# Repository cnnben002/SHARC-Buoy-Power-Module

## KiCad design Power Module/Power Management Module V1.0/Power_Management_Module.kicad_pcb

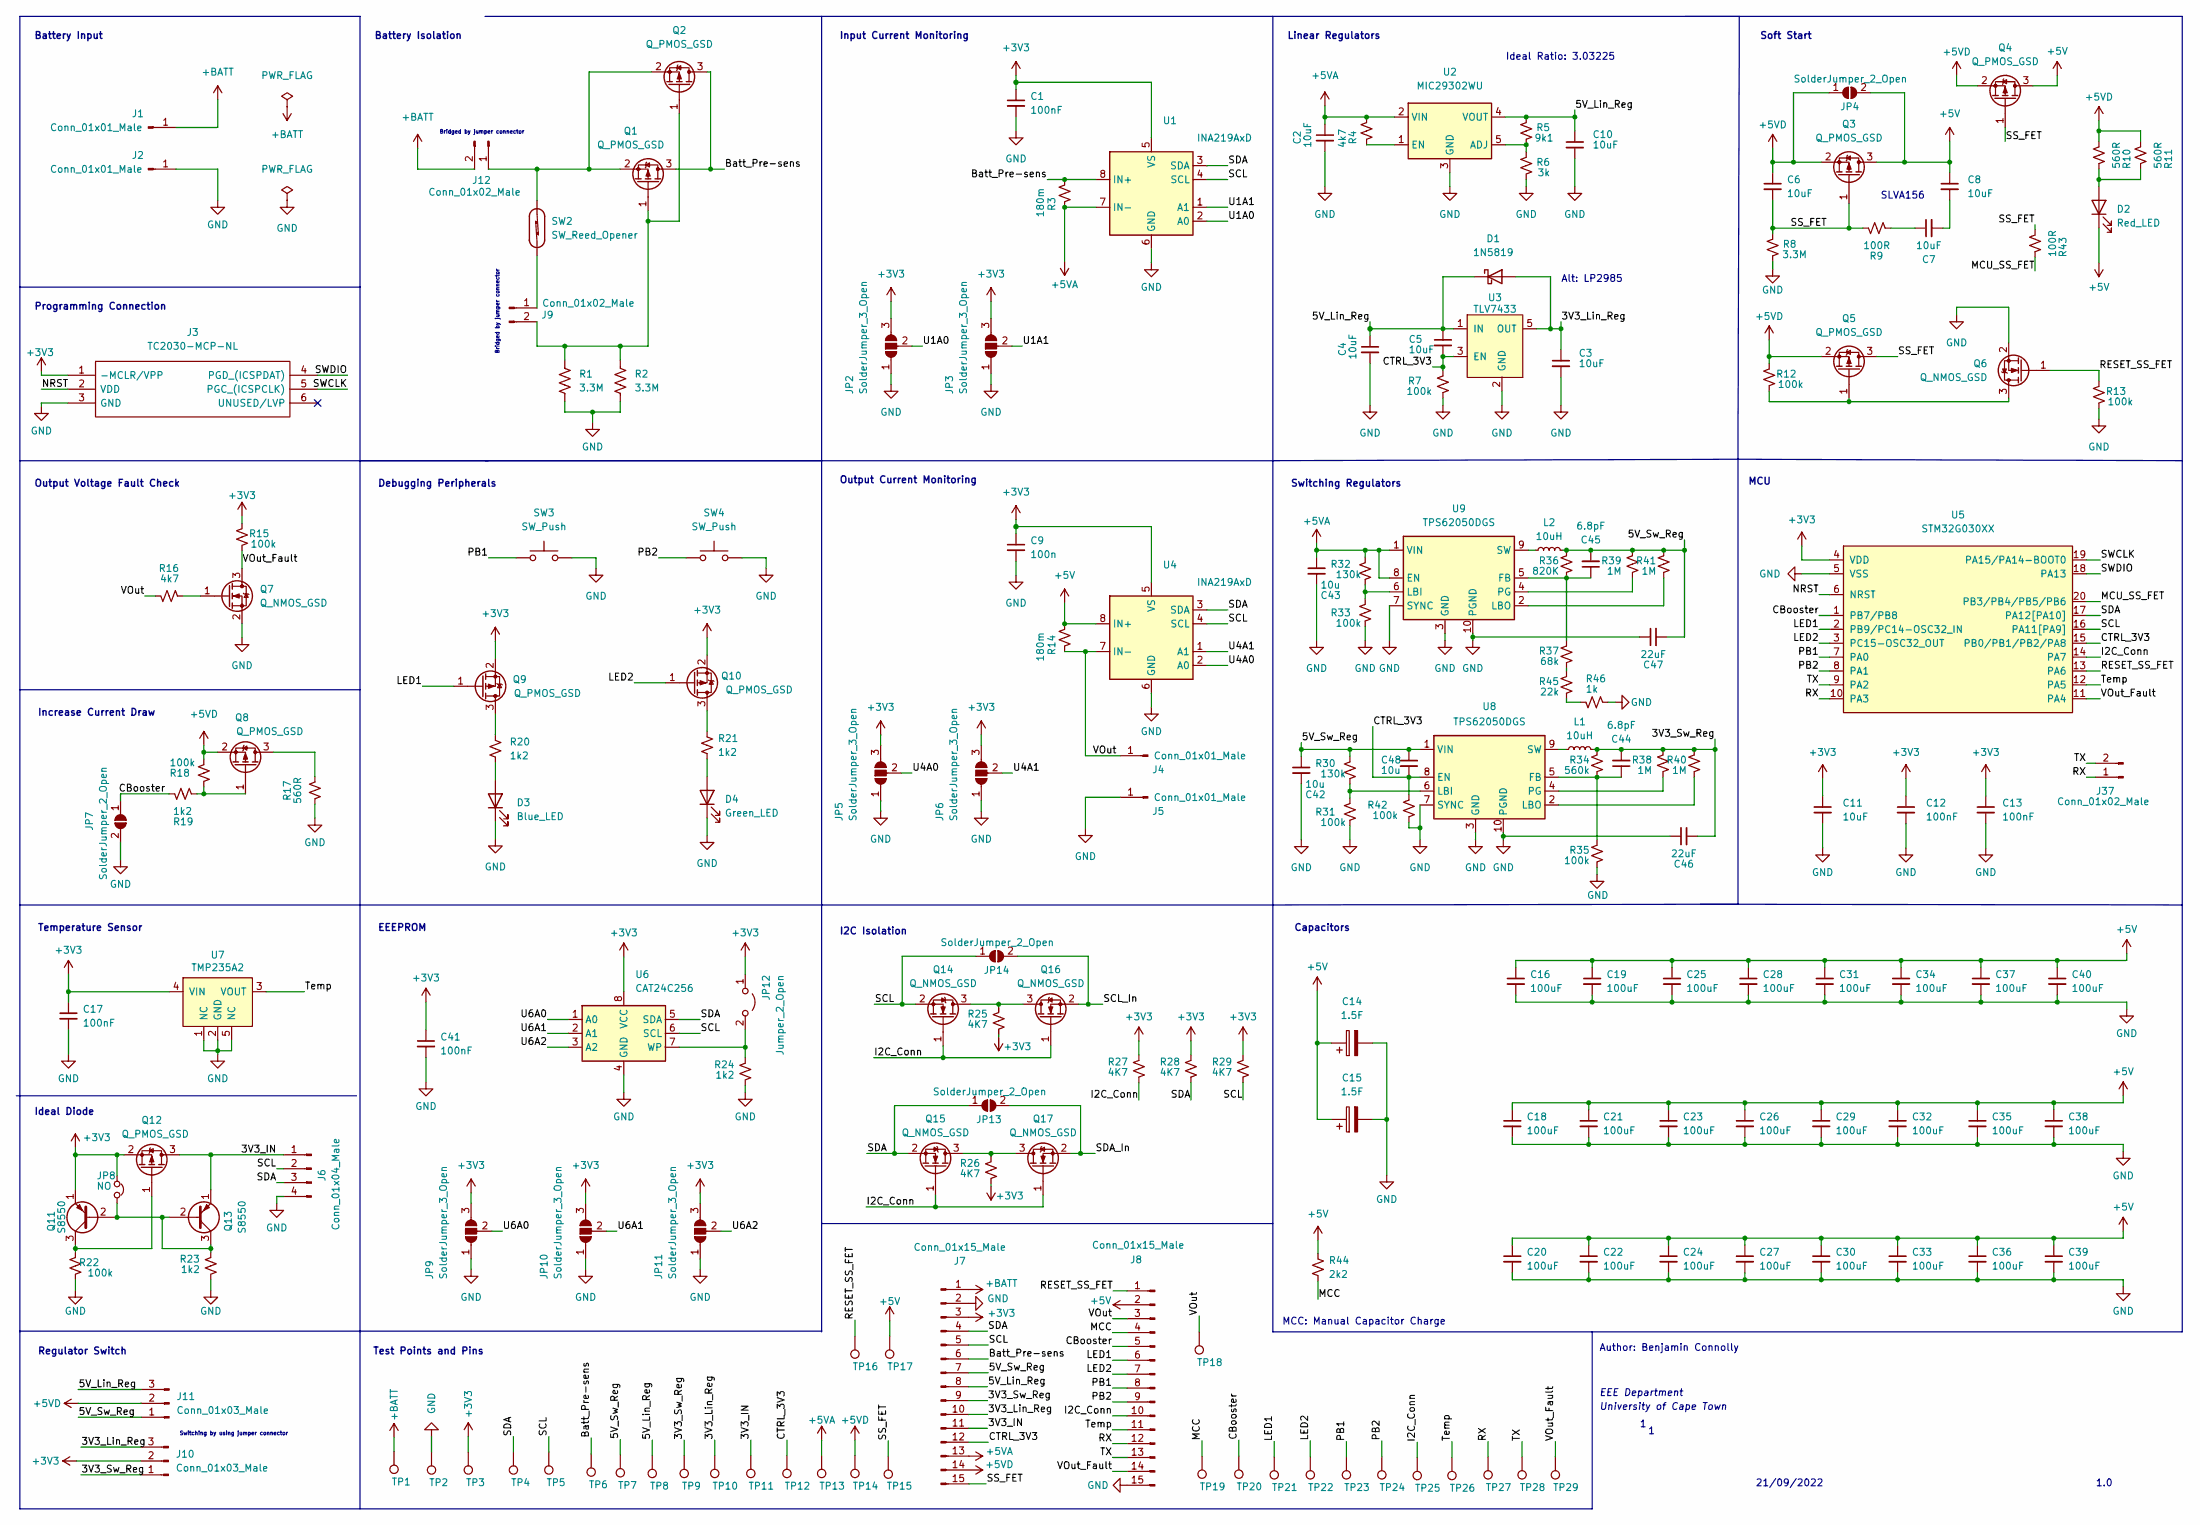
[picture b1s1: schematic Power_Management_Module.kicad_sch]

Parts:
C1, C12, C13, C41: 100nF; C_0402_1005Metric
C2, C3, C4, C5, C6, C7, C8, C10, C11: 10uF; C_0603_1608Metric
C9: 100n; C_0402_1005Metric
C14, C15: 1.5F; SP-5R5-Z155VY
C16, C18, C19, C20, C21, C22, C23, C24, C25, C26, C27, C28, C29, C30, C31, C32, C33, C34, C35, C36, C37, C38, C39, C40: 100uF; C_1206_3216Metric
C17: 100nF; C_1206_3216Metric
C42, C43, C48: 10u; C_0603_1608Metric
C44, C45: 6.8pF; C_0603_1608Metric
C46, C47: 22uF; CP_Elec_6.3x4.9
D1: 1N5819; D_SOD-323
D2: Red_LED; LED_0603_1608Metric
D3: Blue_LED; LED_0603_1608Metric
D4: Green_LED; LED_0603_1608Metric
J1, J2, J4, J5: Conn_01x01_Male; Battery_Pad
J3: TC2030-MCP-NL; Tag-Connect_TC2030-IDC-NL_2x03_P1.27mm_Vertical; Manufacturer_Part_Number TC2030-MCP-NL; Mouser Part Number 579-TC2030-MCP-NL
J6: Conn_01x04_Male; PinHeader_1x04_P2.54mm_Vertical
J7, J8: Conn_01x15_Male; PinHeader_1x15_P2.54mm_Vertical
J9, J12, J37: Conn_01x02_Male; PinHeader_1x02_P2.54mm_Vertical
J10, J11: Conn_01x03_Male; PinHeader_1x03_P2.54mm_Vertical
JP2, JP3, JP5, JP6, JP9, JP10, JP11: SolderJumper_3_Open; SolderJumper-3_P2.0mm_Open_TrianglePad1.0x1.5mm
JP4, JP7, JP13, JP14: SolderJumper_2_Open; SolderJumper-2_P1.3mm_Open_RoundedPad1.0x1.5mm
JP8: NO; SolderJumper-2_P1.3mm_Open_RoundedPad1.0x1.5mm
JP12: Jumper_2_Open; SolderJumper-2_P1.3mm_Open_RoundedPad1.0x1.5mm
L1, L2: 10uH; L_1008_2520Metric_Pad1.43x2.20mm_HandSolder
Q1, Q2, Q3, Q4, Q5, Q8, Q9, Q10, Q12: Q_PMOS_GSD; SOT-23
Q6, Q7, Q14, Q15, Q16, Q17: Q_NMOS_GSD; SOT-23
Q11, Q13: S8550; SOT-23
R1, R2: 3.3M; R_0603_1608Metric
R3, R14: 180m; R_2512_6332Metric; LCSC C25076
R4, R16: 4k7; R_0402_1005Metric; LCSC C25076
R5: 9k1; R_2512_6332Metric_Pad1.40x3.35mm_HandSolder; LCSC C25076
R6: 3k; R_2512_6332Metric_Pad1.40x3.35mm_HandSolder; LCSC C25076
R7, R12, R13, R15, R18, R22, R31, R33, R35, R42: 100k; R_0402_1005Metric; LCSC C25076
R8: 3.3M; R_0603_1608Metric; LCSC C25076
R9, R43: 100R; R_0402_1005Metric; LCSC C25076
R10, R11, R17: 560R; R_0603_1608Metric; LCSC C25076
R19, R23, R24: 1k2; R_0402_1005Metric; LCSC C25076
R20, R21: 1k2; R_0402_1005Metric
R25, R26, R27, R28, R29: 4K7; R_0402_1005Metric; LCSC C25076
R30, R32: 130k; R_2512_6332Metric_Pad1.40x3.35mm_HandSolder; LCSC C25076
R34: 560k; R_0402_1005Metric; LCSC C25076
R36: 820K; R_0402_1005Metric; LCSC C25076
R37: 68k; R_0805_2012Metric; LCSC C25076
R38, R39, R40, R41: 1M; R_1206_3216Metric; LCSC C25076
R44: 2k2; R_0402_1005Metric
R45: 22k; R_0603_1608Metric; LCSC C25076
R46: 1k; R_0805_2012Metric; LCSC C25076
SW2: SW_Reed_Opener; SW_SPST_REED_CUSTOM_1
SW3, SW4: SW_Push; SW_SPST_TL3342
TP1, TP2, TP3, TP4, TP5, TP6, TP7, TP8, TP9, TP10, TP11, TP12, TP13, TP14, TP15, TP16, TP17, TP18, TP19, TP20, TP21, TP22, TP23, TP24, TP25, TP26, TP27, TP28, TP29: TestPoint; TestPoint_Pad_2.0x2.0mm
U1, U4: INA219AxD; SOIC-8_3.9x4.9mm_P1.27mm
U2: MIC29302WU; TO-263-5_TabPin3
U3: TLV7433; SOT-23-5_HandSoldering; LCSC DNP
U5: STM32G030XX; TSSOP-20_4.4x6.5mm_P0.65mm; LCSC C529330
U6: CAT24C256; SOIC-8_3.9x4.9mm_P1.27mm
U7: TMP235A2; SOT-353_SC-70-5; LCSC DNP
U8, U9: TPS62050DGS; VSSOP-10_3x3mm_P0.5mm

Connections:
+3V3: C1.1, C9.1, C11.1, C12.1, C13.1, C17.1, C41.1, J3.1 (-MCLR/VPP), J7.3, J10.2, JP2.3 (B), JP3.3 (B), JP5.3 (B), JP6.3 (B), JP8.2, JP9.3 (B), JP10.3 (B), JP11.3 (B), JP12.1 (A), Q9.2 (S), Q10.2 (S), Q11.1 (E), Q12.2 (S), R15.1, R25.2, R26.2, R27.1, R28.1, R29.1, TP3.1, U1.5 (VS), U4.5 (VS), U5.4 (VDD), U6.8 (VCC), U7.4 (VIN)
+5V: C8.1, C14.1, C15.1, C16.1, C18.1, C19.1, C20.1, C21.1, C22.1, C23.1, C24.1, C25.1, C26.1, C27.1, C28.1, C29.1, C30.1, C31.1, C32.1, C33.1, C34.1, C35.1, C36.1, C37.1, C38.1, C39.1, C40.1, D2.1 (K), J8.2, JP4.2 (B), Q3.3 (D), Q4.3 (D), R14.1, R44.1, TP17.1, U4.8 (IN+)
+5VA: C2.1, C43.1, J7.13, R3.2, R4.1, R32.1, TP13.1, U1.7 (IN-), U2.2 (VIN), U9.1 (VIN), U9.8 (EN)
+5VD: C6.1, J7.14, J11.2, JP4.1 (A), Q3.2 (S), Q4.2 (S), Q5.2 (S), Q8.2 (S), R10.2, R11.2, R12.1, R18.2, TP14.1
+BATT: J1.1, J7.1, J12.2, TP1.1
/3V3_IN: J6.1, J7.11, Q12.3 (D), Q13.1 (E), TP11.1
/3V3_Lin_Reg: C3.1, D1.2 (A), J7.10, J10.3, TP10.1, U3.5 (OUT)
/3V3_Sw_Reg: C44.2, C46.2, J7.9, J10.1, L1.2, R34.1, R38.1, R40.1, TP9.1
/5V_Lin_Reg: C4.1, C5.1, C10.1, D1.1 (K), J7.8, J11.3, R5.1, TP8.1, U2.4 (VOUT), U3.1 (IN)
/5V_Sw_Reg: C42.1, C45.2, C47.2, C48.1, J7.7, J11.1, L2.2, R30.1, R36.1, R39.1, R41.1, TP7.1, U8.1 (VIN)
/Batt_Pre-sens: J7.6, Q1.3 (D), Q2.3 (D), R3.1, TP6.1, U1.8 (IN+)
/CBooster: J8.5, JP7.1 (A), R19.2, TP20.1, U5.1 (PB7/PB8)
/CTRL_3V3: C5.2, C48.2, J7.12, R7.1, R42.1, TP12.1, U3.3 (EN), U5.15 (PB0/PB1/PB2/PA8), U8.8 (EN)
/I2C_Conn: J8.10, Q14.1 (G), Q15.1 (G), Q16.1 (G), Q17.1 (G), R27.2, TP25.1, U5.14 (PA7)
/LED1: J8.6, Q9.1 (G), TP21.1, U5.2 (PB9/PC14-OSC32_IN)
/LED2: J8.7, Q10.1 (G), TP22.1, U5.3 (PC15-OSC32_OUT)
/MCC: J8.4, R44.2, TP19.1
/MCU_SS_FET: R43.1, U5.20 (PB3/PB4/PB5/PB6)
/NRST: J3.2 (VDD), U5.6 (NRST)
/PB1: J8.8, SW3.1, TP23.1, U5.7 (PA0)
/PB2: J8.9, SW4.1, TP24.1, U5.8 (PA1)
/RESET_SS_FET: J8.1, Q6.1 (G), R13.1, TP16.1, U5.13 (PA6)
/RX: J8.12, J37.1, TP27.1, U5.10 (PA3)
/SCL: J6.2, J7.5, JP14.1 (A), Q14.2 (S), R29.2, TP5.1, U1.4 (SCL), U4.4 (SCL), U5.16 (PA11[PA9]), U6.6 (SCL)
/SCL_In: JP14.2 (B), Q16.2 (S)
/SDA: J6.3, J7.4, JP13.1 (A), Q15.2 (S), R28.2, TP4.1, U1.3 (SDA), U4.3 (SDA), U5.17 (PA12[PA10]), U6.5 (SDA)
/SDA_In: JP13.2 (B), Q17.2 (S)
/SS_FET: C6.2, J7.15, Q3.1 (G), Q4.1 (G), Q5.3 (D), R8.1, R9.1, R43.2, TP15.1
/SWCLK: J3.5 (PGC_(ICSPCLK)), U5.19 (PA15/PA14-BOOT0)
/SWDIO: J3.4 (PGD_(ICSPDAT)), U5.18 (PA13)
/TX: J8.13, J37.2, TP28.1, U5.9 (PA2)
/Temp: J8.11, TP26.1, U5.12 (PA5), U7.3 (VOUT)
/U1A0: JP2.2 (C), U1.2 (A0)
/U1A1: JP3.2 (C), U1.1 (A1)
/U4A0: JP5.2 (C), U4.2 (A0)
/U4A1: JP6.2 (C), U4.1 (A1)
/U6A0: JP9.2 (C), U6.1 (A0)
/U6A1: JP10.2 (C), U6.2 (A1)
/U6A2: JP11.2 (C), U6.3 (A2)
/VOut: J4.1, J8.3, R14.2, R16.1, TP18.1, U4.7 (IN-)
/VOut_Fault: J8.14, Q7.3 (D), R15.2, TP29.1, U5.11 (PA4)
GND: C1.2, C2.2, C3.2, C4.2, C9.2, C10.2, C11.2, C12.2, C13.2, C14.2, C15.2, C16.2, C17.2, C18.2, C19.2, C20.2, C21.2, C22.2, C23.2, C24.2, C25.2, C26.2, C27.2, C28.2, C29.2, C30.2, C31.2, C32.2, C33.2, C34.2, C35.2, C36.2, C37.2, C38.2, C39.2, C40.2, C41.2, C42.2, C43.2, C46.1, C47.1, D3.1 (K), D4.1 (K), J2.1, J3.3 (GND), J5.1, J6.4, J7.2, J8.15, JP2.1 (A), JP3.1 (A), JP5.1 (A), JP6.1 (A), JP7.2 (B), JP9.1 (A), JP10.1 (A), JP11.1 (A), Q6.2 (S), Q7.2 (S), R1.2, R2.2, R6.2, R7.2, R8.2, R13.2, R17.1, R22.2, R23.2, R24.2, R31.2, R33.2, R35.2, R42.2, R46.1, SW3.2, SW4.2, TP2.1, U1.6 (GND), U2.3 (GND), U3.2 (GND), U4.6 (GND), U5.5 (VSS), U6.4 (GND), U7.1 (NC), U7.2 (GND), U7.5 (NC), U8.3 (GND), U8.7 (SYNC), U8.10 (PGND), U9.3 (GND), U9.7 (SYNC), U9.10 (PGND)
unnamed: C7.1, R9.2
unnamed: C7.2, C8.2
unnamed: C44.1, R34.2, R35.1, U8.5 (FB)
unnamed: C45.1, R36.2, R37.1, U9.5 (FB)
unnamed: D2.2 (A), R10.1, R11.1
unnamed: D3.2 (A), R20.2
unnamed: D4.2 (A), R21.2
unnamed: J9.1, SW2.2
unnamed: J9.2, Q1.1 (G), Q2.1 (G), R1.1, R2.1
unnamed: J12.1, Q1.2 (S), Q2.2 (S), SW2.1
unnamed: JP8.1, Q11.2 (B), Q13.2 (B), Q13.3 (C), R23.1
unnamed: JP12.2 (B), R24.1, U6.7 (WP)
unnamed: L1.1, U8.9 (SW)
unnamed: L2.1, U9.9 (SW)
unnamed: Q5.1 (G), Q6.3 (D), R12.2
unnamed: Q7.1 (G), R16.2
unnamed: Q8.1 (G), R18.1, R19.1
unnamed: Q8.3 (D), R17.2
unnamed: Q9.3 (D), R20.1
unnamed: Q10.3 (D), R21.1
unnamed: Q11.3 (C), Q12.1 (G), R22.1
unnamed: Q14.3 (D), Q16.3 (D), R25.1
unnamed: Q15.3 (D), Q17.3 (D), R26.1
unnamed: R4.2, U2.1 (EN)
unnamed: R5.2, R6.1, U2.5 (ADJ)
unnamed: R30.2, R31.1, U8.6 (LBI)
unnamed: R32.2, R33.1, U9.6 (LBI)
unnamed: R37.2, R45.1
unnamed: R38.2, U8.4 (PG)
unnamed: R39.2, U9.4 (PG)
unnamed: R40.2, U8.2 (LBO)
unnamed: R41.2, U9.2 (LBO)
unnamed: R45.2, R46.2

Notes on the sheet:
Debugging Peripherals
Programming Connection
Capacitors
Soft Start
Input Current Monitoring
Linear Regulators
Output Current Monitoring
MCU
Output Voltage Fault Check
Battery Input
Ideal Diode
Switching Regulators
I2C Isolation
Alt: LP2985
Regulator Switch
Battery Isolation
21/09/2022
Increase Current Draw
Temperature Sensor
Author: Benjamin Connolly
1.0
Ideal Ratio: 3.03225
Bridged by jumper connector
SLVA156
University of Cape Town
Switching by using jumper connector
Test Points and Pins
MCC: Manual Capacitor Charge
EEEPROM
EEE Department

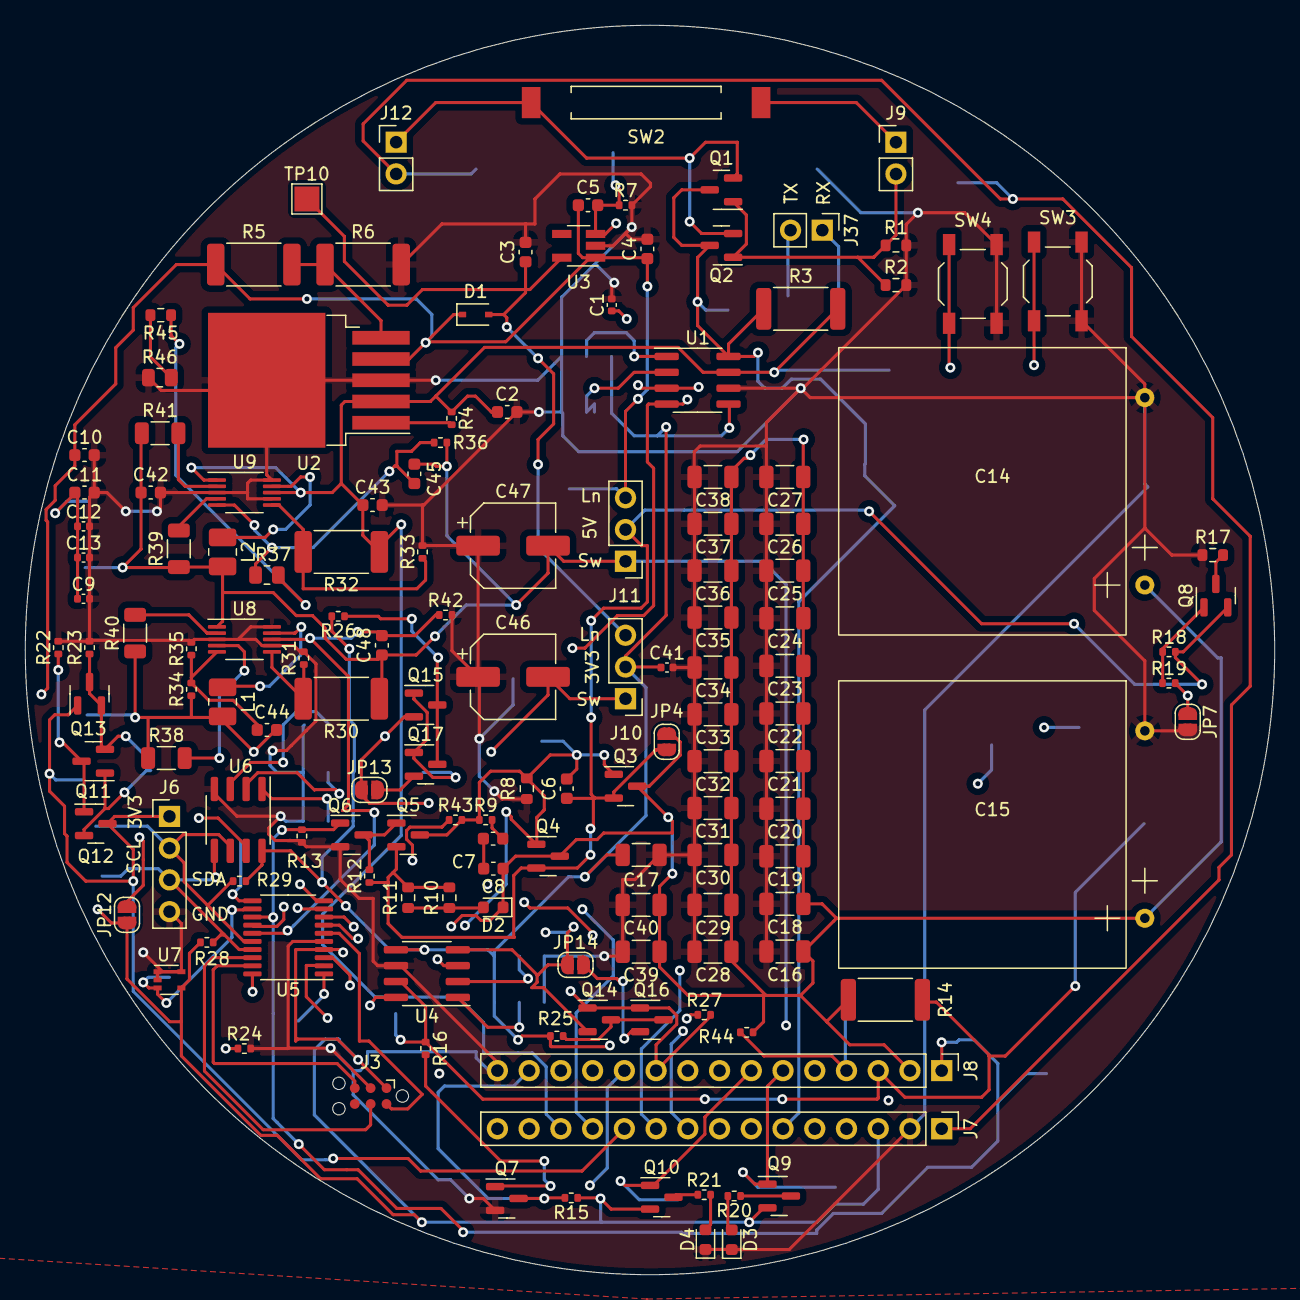
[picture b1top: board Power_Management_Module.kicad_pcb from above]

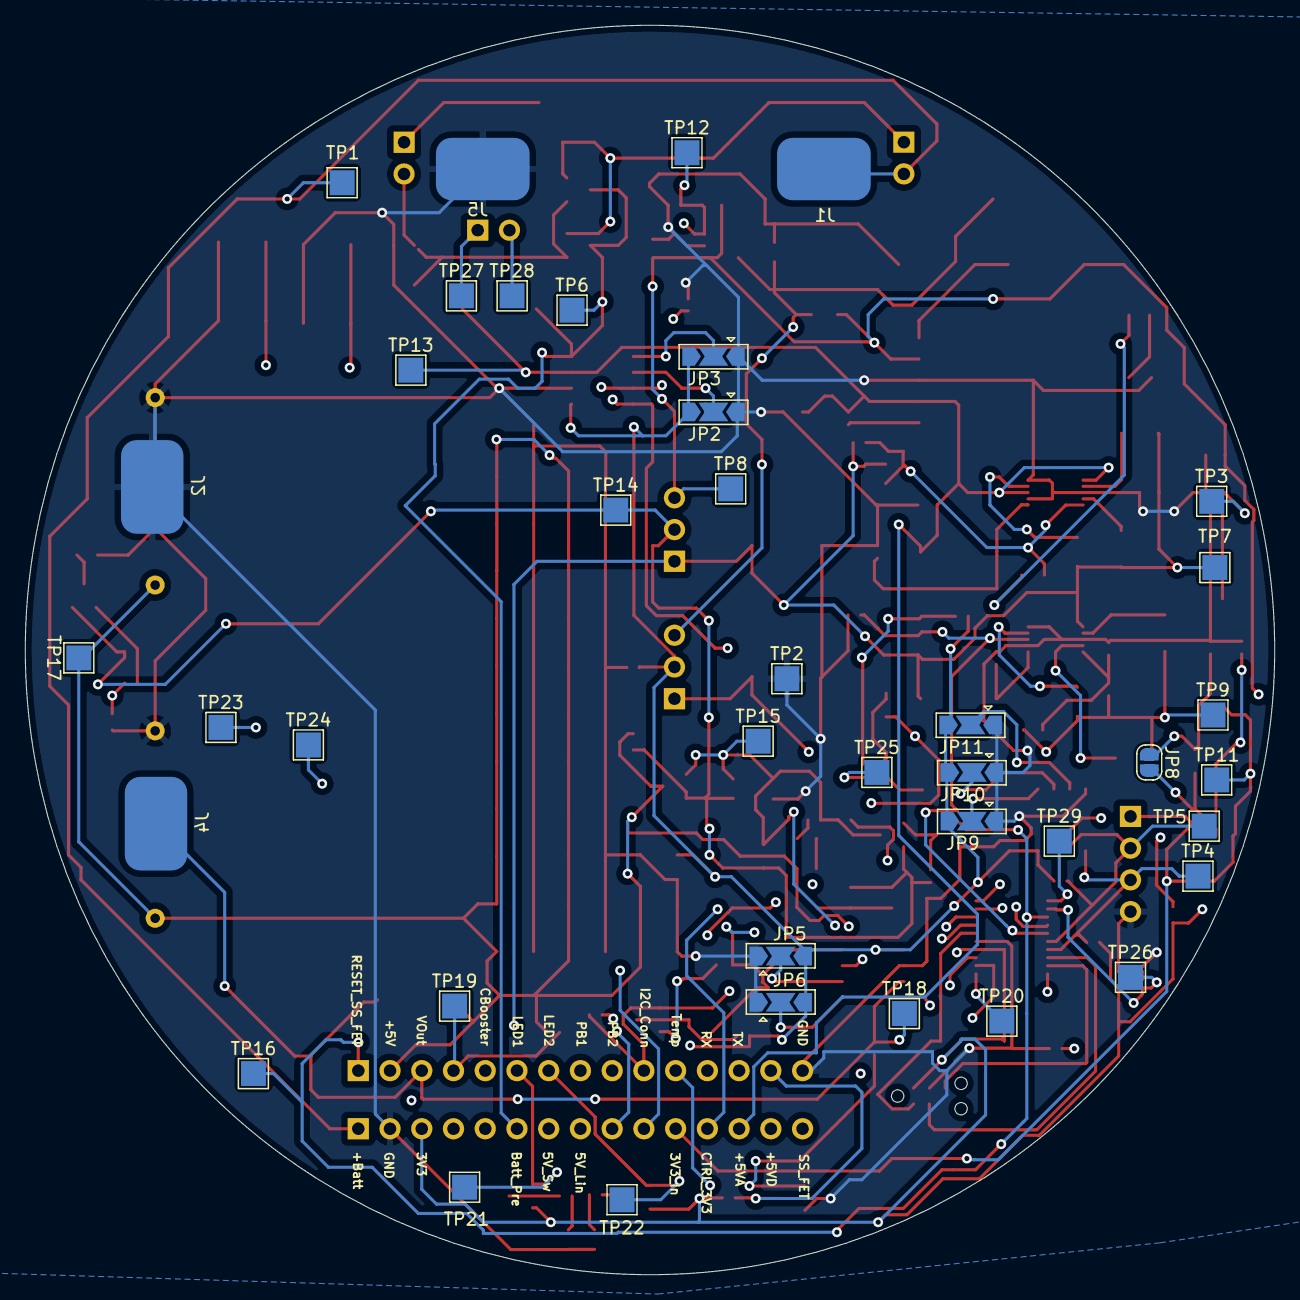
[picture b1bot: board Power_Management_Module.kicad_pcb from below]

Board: 4 copper layers, 100.0 x 100.0 mm, 184 parts (36 on the bottom side), 75 nets.

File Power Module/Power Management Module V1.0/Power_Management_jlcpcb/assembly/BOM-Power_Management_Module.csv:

Comment,Designator,Footprint,LCSC
S8550,"Q11,Q13",SOT-23,C105432
MIC29302WU,U2,TO-263-5_TabPin3,C11149
Conn_01x15_Male,"J7,J8",PinHeader_1x15_P2.54mm_Vertical,C124373
TPS62050DGS,"U8,U9",VSSOP-10_3x3mm_P0.5mm,C128604
560k,R34,R_0402_1005Metric,C132339
Blue_LED,D3,LED_0603_1608Metric,C138547
INA219AxD,"U1,U4",SOIC-8_3.9x4.9mm_P1.27mm,C138706
100uF,"C16,C18,C19,C20,C21,C22,C23,C24,C25,C26,C27,C28,C29,C30,C31,C32,C33,C34,C35,C36,C37,C38,C39,C40",C_1206_3216Metric,C15008
22uF,"C46,C47",CP_Elec_6.3x4.9,C150379
Q_PMOS_GSD,"Q1,Q10,Q12,Q2,Q3,Q4,Q5,Q8,Q9",SOT-23,C15127
6.8pF,"C44,C45",C_0603_1608Metric,C1679
3.3M,"R1,R2,R8",R_0603_1608Metric,C177399
1N5819,D1,D_SOD-323,C191023
Q_NMOS_GSD,"Q14,Q15,Q16,Q17,Q6,Q7",SOT-23,C20917
Red_LED,D2,LED_0603_1608Metric,C2286
100k,"R12,R13,R15,R18,R22,R31,R33,R35,R42,R7",R_0402_1005Metric,C25741
1k2,"R19,R20,R21,R23,R24",R_0402_1005Metric,C25862
4k7,"R16,R25,R26,R27,R28,R29,R4",R_0402_1005Metric,C25900
TMP235A2,U7,SOT-353_SC-70-5,C2868485
100nF,"C1,C12,C13,C17,C41,C9",C_0402_1005Metric,C307331
SW_Push,"SW3,SW4",SW_SPST_TL3342,C318884
22k,R45,R_0603_1608Metric,C325646
68k,R37,R_0805_2012Metric,C352186
560R,"R10,R11,R17",R_0603_1608Metric,C365191
Conn_01x02_Male,"J12,J37,J9",PinHeader_1x02_P2.54mm_Vertical,C390678
Conn_01x03_Male,"J10,J11",PinHeader_1x03_P2.54mm_Vertical,C390679
Conn_01x04_Male,J6,PinHeader_1x04_P2.54mm_Vertical,C390680
TLV7433,U3,SOT-23-5_HandSoldering,C408972
100R,"R43,R9",R_0402_1005Metric,C478864
2k2,R44,R_0402_1005Metric,C478871
1k,R46,R_0805_2012Metric,C479089
1M,"R38,R39,R40,R41",R_1206_3216Metric,C479110
STM32G030XX,U5,TSSOP-20_4.4x6.5mm_P0.65mm,C529330
CAT24C256,U6,SOIC-8_3.9x4.9mm_P1.27mm,C6482
820K,R36,R_0402_1005Metric,C67558
Green_LED,D4,LED_0603_1608Metric,C72043
180m,"R14,R3",R_2512_6332Metric,C76257
10uF,"C10,C11,C2,C3,C4,C42,C43,C48,C5,C6,C7,C8",C_0603_1608Metric,C96446
TC2030-MCP-NL,J3,Tag-Connect_TC2030-IDC-NL_2x03_P1.27mm_Vertical,
TestPoint,TP6,TestPoint_Pad_2.0x2.0mm,
10uH,L2,L_1008_2520Metric_Pad1.43x2.20mm_HandSolder,
TestPoint,TP15,TestPoint_Pad_2.0x2.0mm,
TestPoint,TP25,TestPoint_Pad_2.0x2.0mm,
TestPoint,TP22,TestPoint_Pad_2.0x2.0mm,
SW_Reed_Opener,SW2,SW_SPST_REED_CUSTOM_1,
TestPoint,TP18,TestPoint_Pad_2.0x2.0mm,
TestPoint,TP23,TestPoint_Pad_2.0x2.0mm,
9k1,R5,R_2512_6332Metric_Pad1.40x3.35mm_HandSolder,
TestPoint,TP3,TestPoint_Pad_2.0x2.0mm,
TestPoint,TP14,TestPoint_Pad_2.0x2.0mm,
TestPoint,TP21,TestPoint_Pad_2.0x2.0mm,
TestPoint,TP29,TestPoint_Pad_2.0x2.0mm,
10uH,L1,L_1008_2520Metric_Pad1.43x2.20mm_HandSolder,
Conn_01x01_Male,J1,Battery_Pad,
TestPoint,TP27,TestPoint_Pad_2.0x2.0mm,
TestPoint,TP7,TestPoint_Pad_2.0x2.0mm,
3k,R6,R_2512_6332Metric_Pad1.40x3.35mm_HandSolder,
Conn_01x01_Male,J5,Battery_Pad,
SolderJumper_2_Open,JP7,SolderJumper-2_P1.3mm_Open_RoundedPad1.0x1.5mm,
TestPoint,TP8,TestPoint_Pad_2.0x2.0mm,
TestPoint,TP26,TestPoint_Pad_2.0x2.0mm,
TestPoint,TP10,TestPoint_Pad_2.0x2.0mm,
Conn_01x01_Male,J2,Battery_Pad,
TestPoint,TP13,TestPoint_Pad_2.0x2.0mm,
TestPoint,TP17,TestPoint_Pad_2.0x2.0mm,
1.5F,C15,SP-5R5-Z155VY,
TestPoint,TP5,TestPoint_Pad_2.0x2.0mm,
SolderJumper_2_Open,JP4,SolderJumper-2_P1.3mm_Open_RoundedPad1.0x1.5mm,
TestPoint,TP12,TestPoint_Pad_2.0x2.0mm,
TestPoint,TP4,TestPoint_Pad_2.0x2.0mm,
TestPoint,TP19,TestPoint_Pad_2.0x2.0mm,
SolderJumper_2_Open,JP13,SolderJumper-2_P1.3mm_Open_RoundedPad1.0x1.5mm,
130k,R30,R_2512_6332Metric_Pad1.40x3.35mm_HandSolder,
1.5F,C14,SP-5R5-Z155VY,
SolderJumper_2_Open,JP14,SolderJumper-2_P1.3mm_Open_RoundedPad1.0x1.5mm,
TestPoint,TP11,TestPoint_Pad_2.0x2.0mm,
TestPoint,TP1,TestPoint_Pad_2.0x2.0mm,
TestPoint,TP2,TestPoint_Pad_2.0x2.0mm,
130k,R32,R_2512_6332Metric_Pad1.40x3.35mm_HandSolder,
TestPoint,TP28,TestPoint_Pad_2.0x2.0mm,
Conn_01x01_Male,J4,Battery_Pad,
TestPoint,TP16,TestPoint_Pad_2.0x2.0mm,
TestPoint,TP20,TestPoint_Pad_2.0x2.0mm,
TestPoint,TP24,TestPoint_Pad_2.0x2.0mm,
Jumper_2_Open,JP12,SolderJumper-2_P1.3mm_Open_RoundedPad1.0x1.5mm,
NO,JP8,SolderJumper-2_P1.3mm_Open_RoundedPad1.0x1.5mm,
SolderJumper_3_Open,JP10,SolderJumper-3_P2.0mm_Open_TrianglePad1.0x1.5mm,
SolderJumper_3_Open,JP6,SolderJumper-3_P2.0mm_Open_TrianglePad1.0x1.5mm,
SolderJumper_3_Open,JP3,SolderJumper-3_P2.0mm_Open_TrianglePad1.0x1.5mm,
SolderJumper_3_Open,JP9,SolderJumper-3_P2.0mm_Open_TrianglePad1.0x1.5mm,
SolderJumper_3_Open,JP5,SolderJumper-3_P2.0mm_Open_TrianglePad1.0x1.5mm,
SolderJumper_3_Open,JP2,SolderJumper-3_P2.0mm_Open_TrianglePad1.0x1.5mm,
TestPoint,TP9,TestPoint_Pad_2.0x2.0mm,
SolderJumper_3_Open,JP11,SolderJumper-3_P2.0mm_Open_TrianglePad1.0x1.5mm,

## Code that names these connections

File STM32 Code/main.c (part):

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  MX_ADC1_Init();
  MX_USART2_UART_Init();
  /* USER CODE BEGIN 2 */
  HAL_GPIO_WritePin(CTRL_3V3_GPIO_Port, CTRL_3V3_Pin, GPIO_PIN_SET); //Setting the system to give itself 3.3 volts
  HAL_GPIO_WritePin(LED1_GPIO_Port, LED1_Pin, GPIO_PIN_SET);
  HAL_GPIO_WritePin(LED2_GPIO_Port, LED2_Pin, GPIO_PIN_RESET);
  /* USER CODE END 2 */

  /* Infinite loop */
  /* USER CODE BEGIN WHILE */
  while (1)
  {
	  HAL_GPIO_TogglePin(LED1_GPIO_Port, LED1_Pin);
	  HAL_GPIO_TogglePin(LED2_GPIO_Port, LED2_Pin);
	  HAL_Delay(500);
    /* USER CODE END WHILE */

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  __HAL_RCC_GPIOB_CLK_ENABLE();

  /*Configure GPIO pin Output Level */
  HAL_GPIO_WritePin(GPIOC, LED1_Pin|LED2_Pin, GPIO_PIN_RESET);

  /*Configure GPIO pin Output Level */
  HAL_GPIO_WritePin(GPIOA, VOUT_FAULT_Pin|Reset_SS_FET_Pin|I2C_Connect_Pin, GPIO_PIN_RESET);

  /*Configure GPIO pin Output Level */
  HAL_GPIO_WritePin(GPIOB, CTRL_3V3_Pin|MCU_SS_FET_Pin, GPIO_PIN_RESET);

  /*Configure GPIO pins : LED1_Pin LED2_Pin */
  GPIO_InitStruct.Pin = LED1_Pin|LED2_Pin;
  GPIO_InitStruct.Mode = GPIO_MODE_OUTPUT_PP;
  GPIO_InitStruct.Pull = GPIO_NOPULL;
  GPIO_InitStruct.Speed = GPIO_SPEED_FREQ_LOW;
  HAL_GPIO_Init(GPIOC, &GPIO_InitStruct);

  /*Configure GPIO pins : PB0_Pin PB1_Pin */
  GPIO_InitStruct.Pin = PB0_Pin|PB1_Pin;
  GPIO_InitStruct.Mode = GPIO_MODE_INPUT;
  GPIO_InitStruct.Pull = GPIO_NOPULL;
  HAL_GPIO_Init(GPIOA, &GPIO_InitStruct);

  /*Configure GPIO pins : VOUT_FAULT_Pin Reset_SS_FET_Pin I2C_Connect_Pin */
  GPIO_InitStruct.Pin = VOUT_FAULT_Pin|Reset_SS_FET_Pin|I2C_Connect_Pin;
  GPIO_InitStruct.Mode = GPIO_MODE_OUTPUT_PP;
  GPIO_InitStruct.Pull = GPIO_NOPULL;
  GPIO_InitStruct.Speed = GPIO_SPEED_FREQ_LOW;
  HAL_GPIO_Init(GPIOA, &GPIO_InitStruct);

  /*Configure GPIO pins : CTRL_3V3_Pin MCU_SS_FET_Pin */
  GPIO_InitStruct.Pin = CTRL_3V3_Pin|MCU_SS_FET_Pin;
  GPIO_InitStruct.Mode = GPIO_MODE_OUTPUT_PP;
  GPIO_InitStruct.Pull = GPIO_NOPULL;
  GPIO_InitStruct.Speed = GPIO_SPEED_FREQ_LOW;
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
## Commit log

2022-11-06 Upload files
    Upload files

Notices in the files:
STM32 Code/main.c:
Copyright (c) 2022 STMicroelectronics.
All rights reserved.
This software is licensed under terms that can be found in the LICENSE file
